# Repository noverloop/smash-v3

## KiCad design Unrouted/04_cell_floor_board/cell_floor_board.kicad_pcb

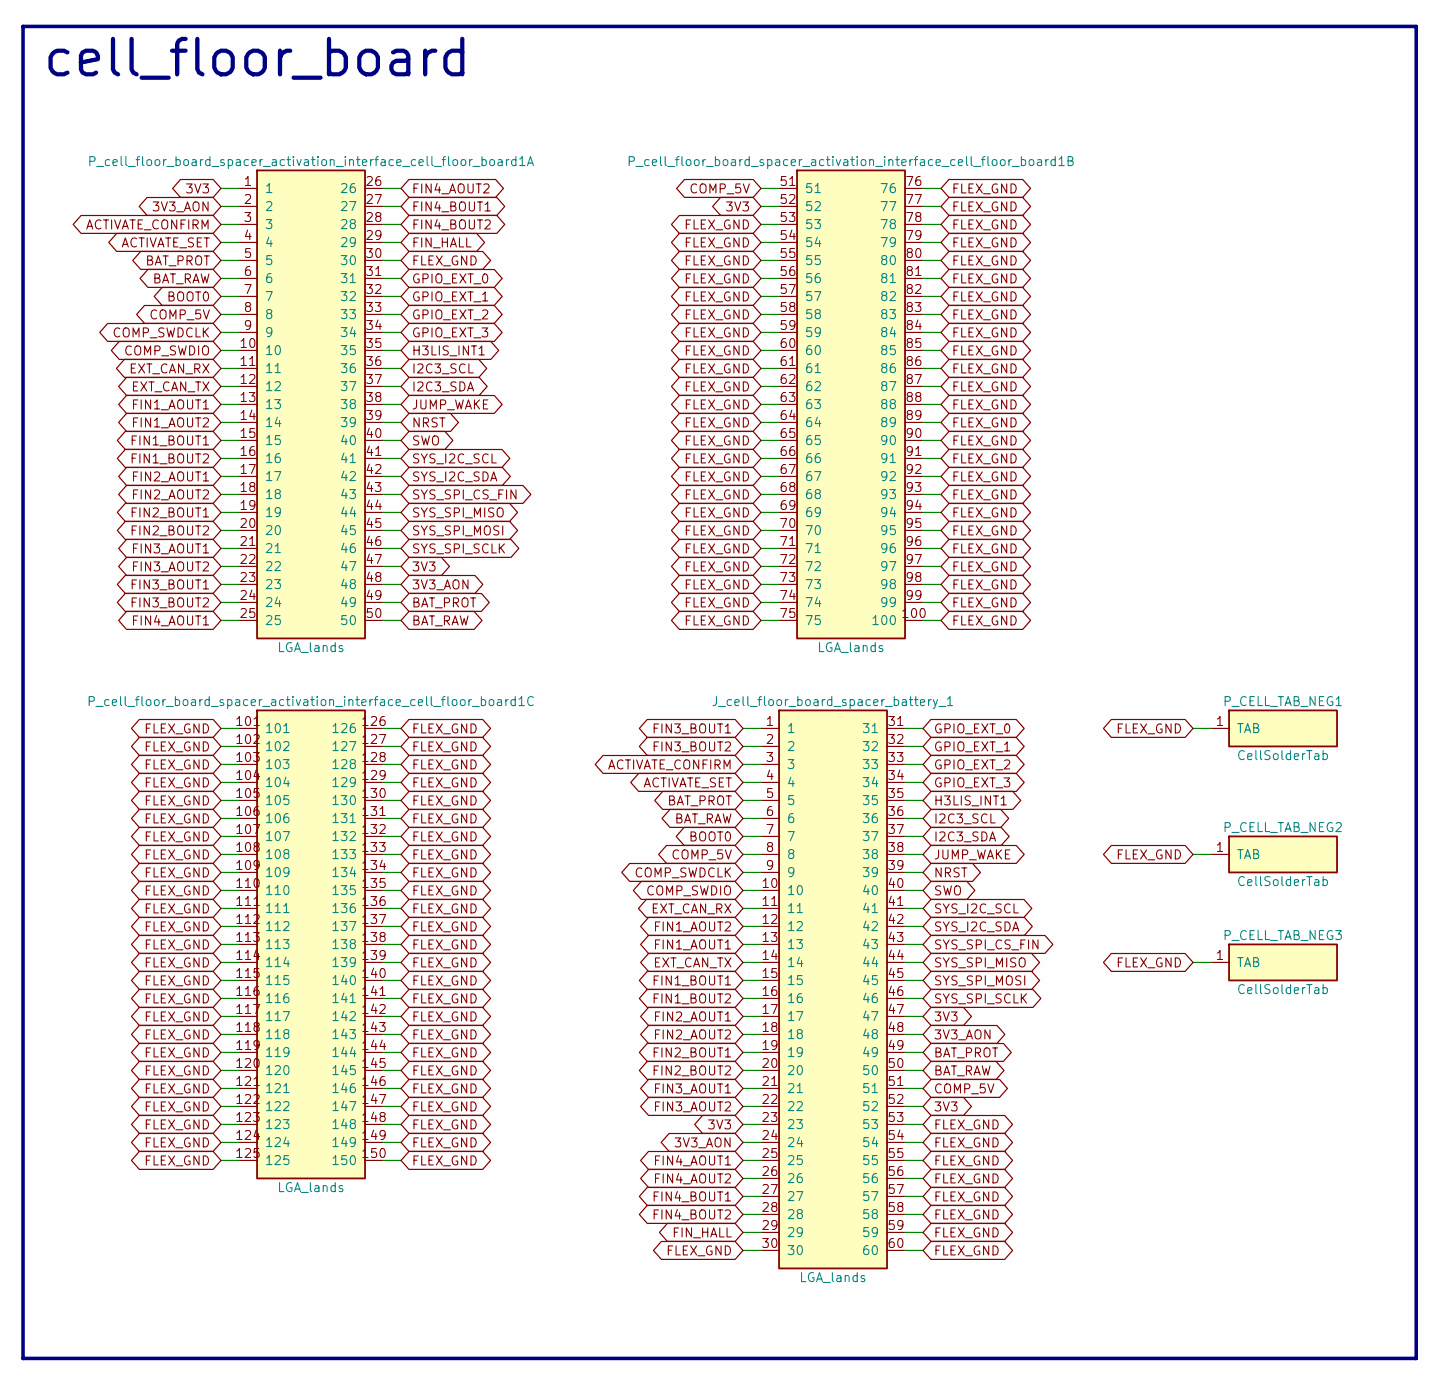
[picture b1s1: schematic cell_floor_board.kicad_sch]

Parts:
J_cell_floor_board_spacer_battery_1: LGA_lands; J_cell_floor_board_spacer_battery_1; MPN LGA_lands
P_CELL_TAB_NEG1, P_CELL_TAB_NEG2, P_CELL_TAB_NEG3: CellSolderTab; CellSolderTab_placeholder; MPN CellSolderTab
P_cell_floor_board_spacer_activation_interface_cell_floor_board1: LGA_lands; P_cell_floor_board_spacer_activation_interface_cell_floor_b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; MPN LGA_lands

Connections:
3V3: J_cell_floor_board_spacer_battery_1.23, J_cell_floor_board_spacer_battery_1.47, J_cell_floor_board_spacer_battery_1.52, P_cell_floor_board_spacer_activation_in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.1, P_cell_floor_board_spacer_activation_in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.47, P_cell_floor_board_spacer_activation_in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.52
3V3_AON: J_cell_floor_board_spacer_battery_1.24, J_cell_floor_board_spacer_battery_1.48, P_cell_floor_board_spacer_activation_in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.2, P_cell_floor_board_spacer_activation_in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.48
ACTIVATE_CONFIRM: J_cell_floor_board_spacer_battery_1.3, P_cell_floor_board_spacer_activation_in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.3
ACTIVATE_SET: J_cell_floor_board_spacer_battery_1.4, P_cell_floor_board_spacer_activation_in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.4
BAT_PROT: J_cell_floor_board_spacer_battery_1.5, J_cell_floor_board_spacer_battery_1.49, P_cell_floor_board_spacer_activation_in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.5, P_cell_floor_board_spacer_activation_in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.49
BAT_RAW: J_cell_floor_board_spacer_battery_1.6, J_cell_floor_board_spacer_battery_1.50, P_cell_floor_board_spacer_activation_in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.6, P_cell_floor_board_spacer_activation_in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.50
BOOT0: J_cell_floor_board_spacer_battery_1.7, P_cell_floor_board_spacer_activation_in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.7
COMP_5V: J_cell_floor_board_spacer_battery_1.8, J_cell_floor_board_spacer_battery_1.51, P_cell_floor_board_spacer_activation_in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.8, P_cell_floor_board_spacer_activation_in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.51
COMP_SWDCLK: J_cell_floor_board_spacer_battery_1.9, P_cell_floor_board_spacer_activation_in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.9
COMP_SWDIO: J_cell_floor_board_spacer_battery_1.10, P_cell_floor_board_spacer_activation_in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.10
EXT_CAN_RX: J_cell_floor_board_spacer_battery_1.11, P_cell_floor_board_spacer_activation_in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.11
EXT_CAN_TX: J_cell_floor_board_spacer_battery_1.14, P_cell_floor_board_spacer_activation_in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.12
FIN1_AOUT1: J_cell_floor_board_spacer_battery_1.13, P_cell_floor_board_spacer_activation_in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.13
FIN1_AOUT2: J_cell_floor_board_spacer_battery_1.12, P_cell_floor_board_spacer_activation_in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.14
FIN1_BOUT1: J_cell_floor_board_spacer_battery_1.15, P_cell_floor_board_spacer_activation_in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.15
FIN1_BOUT2: J_cell_floor_board_spacer_battery_1.16, P_cell_floor_board_spacer_activation_in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.16
FIN2_AOUT1: J_cell_floor_board_spacer_battery_1.17, P_cell_floor_board_spacer_activation_in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.17
FIN2_AOUT2: J_cell_floor_board_spacer_battery_1.18, P_cell_floor_board_spacer_activation_in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.18
FIN2_BOUT1: J_cell_floor_board_spacer_battery_1.19, P_cell_floor_board_spacer_activation_in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.19
FIN2_BOUT2: J_cell_floor_board_spacer_battery_1.20, P_cell_floor_board_spacer_activation_in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.20
FIN3_AOUT1: J_cell_floor_board_spacer_battery_1.21, P_cell_floor_board_spacer_activation_in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.21
FIN3_AOUT2: J_cell_floor_board_spacer_battery_1.22, P_cell_floor_board_spacer_activation_in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.22
FIN3_BOUT1: J_cell_floor_board_spacer_battery_1.1, P_cell_floor_board_spacer_activation_in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.23
FIN3_BOUT2: J_cell_floor_board_spacer_battery_1.2, P_cell_floor_board_spacer_activation_in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.24
FIN4_AOUT1: J_cell_floor_board_spacer_battery_1.25, P_cell_floor_board_spacer_activation_in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.25
FIN4_AOUT2: J_cell_floor_board_spacer_battery_1.26, P_cell_floor_board_spacer_activation_in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.26
FIN4_BOUT1: J_cell_floor_board_spacer_battery_1.27, P_cell_floor_board_spacer_activation_in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.27
FIN4_BOUT2: J_cell_floor_board_spacer_battery_1.28, P_cell_floor_board_spacer_activation_in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.28
FIN_HALL: J_cell_floor_board_spacer_battery_1.29, P_cell_floor_board_spacer_activation_in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.29
FLEX_GND: J_cell_floor_board_spacer_battery_1.30, J_cell_floor_board_spacer_battery_1.53, J_cell_floor_board_spacer_battery_1.54, J_cell_floor_board_spacer_battery_1.55, J_cell_floor_board_spacer_battery_1.56, J_cell_floor_board_spacer_battery_1.57, J_cell_floor_board_spacer_battery_1.58, J_cell_floor_board_spacer_battery_1.59, J_cell_floor_board_spacer_battery_1.60, P_CELL_TAB_NEG1.1, P_CELL_TAB_NEG2.1, P_CELL_TAB_NEG3.1, P_cell_floor_board_spacer_activation_in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.30, P_cell_floor_board_spacer_activation_in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.53, P_cell_floor_board_spacer_activation_in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.54, P_cell_floor_board_spacer_activation_in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.55, P_cell_floor_board_spacer_activation_in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.56, P_cell_floor_board_spacer_activation_in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.57, P_cell_floor_board_spacer_activation_in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.58, P_cell_floor_board_spacer_activation_in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.59, P_cell_floor_board_spacer_activation_in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.60, P_cell_floor_board_spacer_activation_in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.61, P_cell_floor_board_spacer_activation_in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.62, P_cell_floor_board_spacer_activation_in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.63, P_cell_floor_board_spacer_activation_in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.64, P_cell_floor_board_spacer_activation_in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.65, P_cell_floor_board_spacer_activation_in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.66, P_cell_floor_board_spacer_activation_in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.67, P_cell_floor_board_spacer_activation_in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.68, P_cell_floor_board_spacer_activation_in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.69, P_cell_floor_board_spacer_activation_in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.70, P_cell_floor_board_spacer_activation_in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.71, P_cell_floor_board_spacer_activation_in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.72, P_cell_floor_board_spacer_activation_in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.73, P_cell_floor_board_spacer_activation_in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.74, P_cell_floor_board_spacer_activation_in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.75, P_cell_floor_board_spacer_activation_in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.76, P_cell_floor_board_spacer_activation_in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.77, P_cell_floor_board_spacer_activation_in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.78, P_cell_floor_board_spacer_activation_in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.79, P_cell_floor_board_spacer_activation_in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.80, P_cell_floor_board_spacer_activation_in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.81, P_cell_floor_board_spacer_activation_in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.82, P_cell_floor_board_spacer_activation_in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.83, P_cell_floor_board_spacer_activation_in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.84, P_cell_floor_board_spacer_activation_in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.85, P_cell_floor_board_spacer_activation_in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.86, P_cell_floor_board_spacer_activation_in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.87, P_cell_floor_board_spacer_activation_in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.88, P_cell_floor_board_spacer_activation_in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.89, P_cell_floor_board_spacer_activation_in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.90, P_cell_floor_board_spacer_activation_in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.91, P_cell_floor_board_spacer_activation_in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.92, P_cell_floor_board_spacer_activation_in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.93, P_cell_floor_board_spacer_activation_in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.94, P_cell_floor_board_spacer_activation_in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.95, P_cell_floor_board_spacer_activation_in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.96, P_cell_floor_board_spacer_activation_in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.97, P_cell_floor_board_spacer_activation_in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.98, P_cell_floor_board_spacer_activation_in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.99, P_cell_floor_board_spacer_activation_in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.100, P_cell_floor_board_spacer_activation_in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.101, P_cell_floor_board_spacer_activation_in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.102, P_cell_floor_board_spacer_activation_in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.103, P_cell_floor_board_spacer_activation_in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.104, P_cell_floor_board_spacer_activation_in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.105, P_cell_floor_board_spacer_activation_in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.106, P_cell_floor_board_spacer_activation_in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.107, P_cell_floor_board_spacer_activation_in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.108, P_cell_floor_board_spacer_activation_in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.109, P_cell_floor_board_spacer_activation_in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.110, P_cell_floor_board_spacer_activation_in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.111, P_cell_floor_board_spacer_activation_in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.112, P_cell_floor_board_spacer_activation_in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.113, P_cell_floor_board_spacer_activation_in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.114, P_cell_floor_board_spacer_activation_in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.115, P_cell_floor_board_spacer_activation_in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.116, P_cell_floor_board_spacer_activation_in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.117, P_cell_floor_board_spacer_activation_in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.118, P_cell_floor_board_spacer_activation_in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.119, P_cell_floor_board_spacer_activation_in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.120, P_cell_floor_board_spacer_activation_in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.121, P_cell_floor_board_spacer_activation_in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.122, P_cell_floor_board_spacer_activation_in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.123, P_cell_floor_board_spacer_activation_in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.124, P_cell_floor_board_spacer_activation_in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.125, P_cell_floor_board_spacer_activation_in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.126, P_cell_floor_board_spacer_activation_in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.127, P_cell_floor_board_spacer_activation_in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.128, P_cell_floor_board_spacer_activation_in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.129, P_cell_floor_board_spacer_activation_in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.130, P_cell_floor_board_spacer_activation_in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.131, P_cell_floor_board_spacer_activation_in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.132, P_cell_floor_board_spacer_activation_in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.133, P_cell_floor_board_spacer_activation_in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.134, P_cell_floor_board_spacer_activation_in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.135, P_cell_floor_board_spacer_activation_in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.136, P_cell_floor_board_spacer_activation_in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.137, P_cell_floor_board_spacer_activation_in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.138, P_cell_floor_board_spacer_activation_in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.139, P_cell_floor_board_spacer_activation_in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.140, P_cell_floor_board_spacer_activation_in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.141, P_cell_floor_board_spacer_activation_in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.142, P_cell_floor_board_spacer_activation_in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.143, P_cell_floor_board_spacer_activation_in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.144, P_cell_floor_board_spacer_activation_in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.145, P_cell_floor_board_spacer_activation_in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.146, P_cell_floor_board_spacer_activation_in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.147, P_cell_floor_board_spacer_activation_in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.148, P_cell_floor_board_spacer_activation_in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.149, P_cell_floor_board_spacer_activation_in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.150
GPIO_EXT_0: J_cell_floor_board_spacer_battery_1.31, P_cell_floor_board_spacer_activation_in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.31
GPIO_EXT_1: J_cell_floor_board_spacer_battery_1.32, P_cell_floor_board_spacer_activation_in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.32
GPIO_EXT_2: J_cell_floor_board_spacer_battery_1.33, P_cell_floor_board_spacer_activation_in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.33
GPIO_EXT_3: J_cell_floor_board_spacer_battery_1.34, P_cell_floor_board_spacer_activation_in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.34
H3LIS_INT1: J_cell_floor_board_spacer_battery_1.35, P_cell_floor_board_spacer_activation_in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.35
I2C3_SCL: J_cell_floor_board_spacer_battery_1.36, P_cell_floor_board_spacer_activation_in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.36
I2C3_SDA: J_cell_floor_board_spacer_battery_1.37, P_cell_floor_board_spacer_activation_in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.37
JUMP_WAKE: J_cell_floor_board_spacer_battery_1.38, P_cell_floor_board_spacer_activation_in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.38
NRST: J_cell_floor_board_spacer_battery_1.39, P_cell_floor_board_spacer_activation_in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.39
SWO: J_cell_floor_board_spacer_battery_1.40, P_cell_floor_board_spacer_activation_in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.40
SYS_I2C_SCL: J_cell_floor_board_spacer_battery_1.41, P_cell_floor_board_spacer_activation_in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.41
SYS_I2C_SDA: J_cell_floor_board_spacer_battery_1.42, P_cell_floor_board_spacer_activation_in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.42
SYS_SPI_CS_FIN: J_cell_floor_board_spacer_battery_1.43, P_cell_floor_board_spacer_activation_in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.43
SYS_SPI_MISO: J_cell_floor_board_spacer_battery_1.44, P_cell_floor_board_spacer_activation_in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.44
SYS_SPI_MOSI: J_cell_floor_board_spacer_battery_1.45, P_cell_floor_board_spacer_activation_in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.45
SYS_SPI_SCLK: J_cell_floor_board_spacer_battery_1.46, P_cell_floor_board_spacer_activation_in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.46

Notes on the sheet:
cell_floor_board

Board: 6 copper layers, 7 parts (1 on the bottom side), 46 nets, no tracks yet.

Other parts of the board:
MH1, MH2: smash_mech_potting

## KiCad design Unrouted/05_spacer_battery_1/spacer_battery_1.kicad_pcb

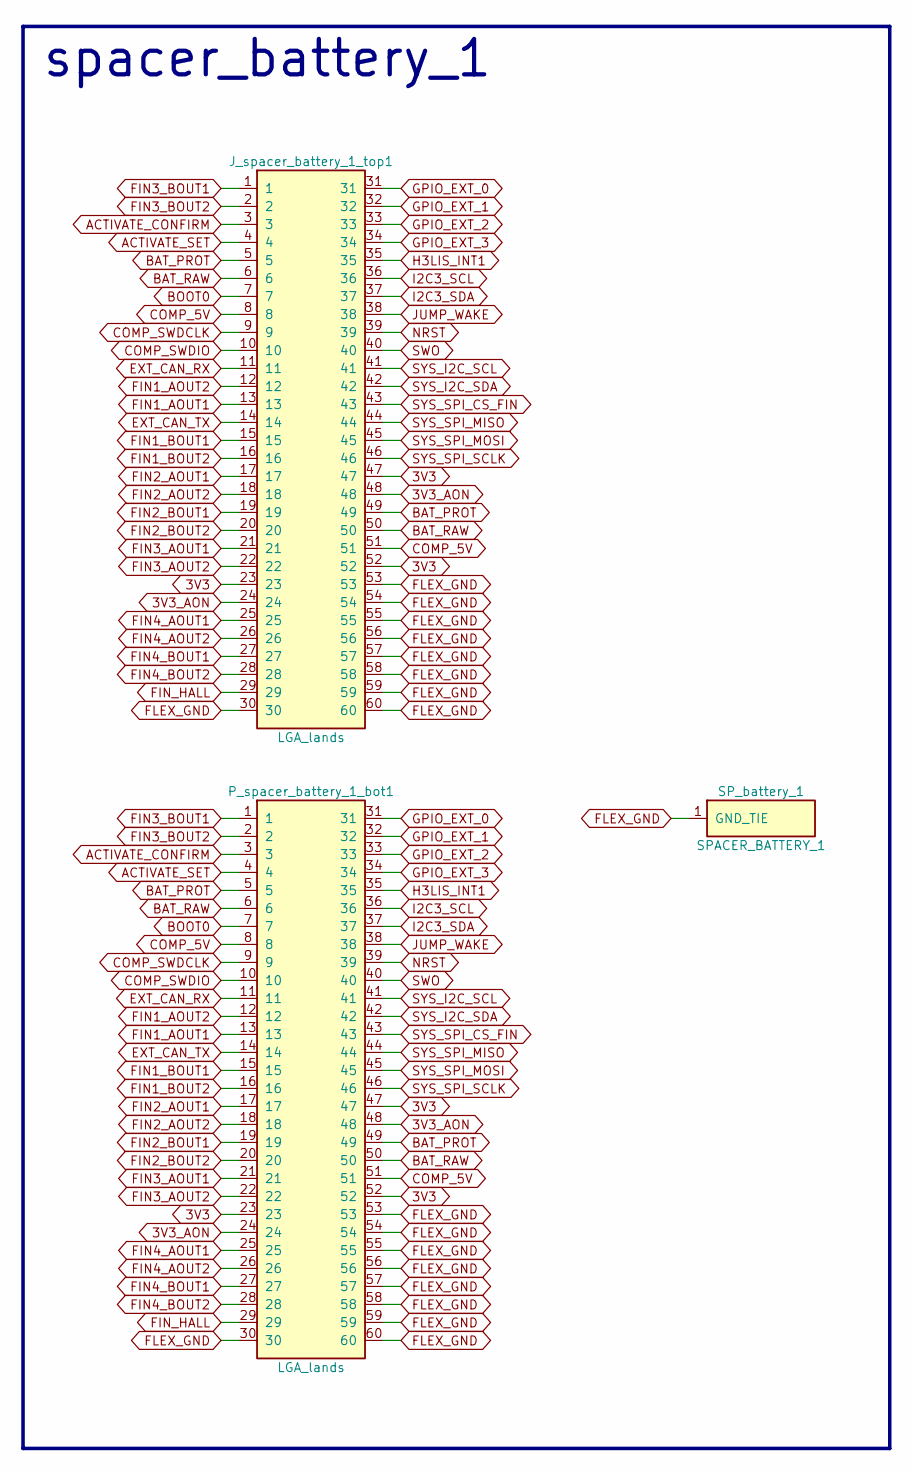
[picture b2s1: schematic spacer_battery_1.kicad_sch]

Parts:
J_spacer_battery_1_top1: LGA_lands; J_spacer_battery_1_top; MPN LGA_lands
P_spacer_battery_1_bot1: LGA_lands; P_spacer_battery_1_bot; MPN LGA_lands
SP_battery_1: SPACER_BATTERY_1; Spacer_Mechanical_34mm

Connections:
3V3: J_spacer_battery_1_top1.23, J_spacer_battery_1_top1.47, J_spacer_battery_1_top1.52, P_spacer_battery_1_bot1.23, P_spacer_battery_1_bot1.47, P_spacer_battery_1_bot1.52
3V3_AON: J_spacer_battery_1_top1.24, J_spacer_battery_1_top1.48, P_spacer_battery_1_bot1.24, P_spacer_battery_1_bot1.48
ACTIVATE_CONFIRM: J_spacer_battery_1_top1.3, P_spacer_battery_1_bot1.3
ACTIVATE_SET: J_spacer_battery_1_top1.4, P_spacer_battery_1_bot1.4
BAT_PROT: J_spacer_battery_1_top1.5, J_spacer_battery_1_top1.49, P_spacer_battery_1_bot1.5, P_spacer_battery_1_bot1.49
BAT_RAW: J_spacer_battery_1_top1.6, J_spacer_battery_1_top1.50, P_spacer_battery_1_bot1.6, P_spacer_battery_1_bot1.50
BOOT0: J_spacer_battery_1_top1.7, P_spacer_battery_1_bot1.7
COMP_5V: J_spacer_battery_1_top1.8, J_spacer_battery_1_top1.51, P_spacer_battery_1_bot1.8, P_spacer_battery_1_bot1.51
COMP_SWDCLK: J_spacer_battery_1_top1.9, P_spacer_battery_1_bot1.9
COMP_SWDIO: J_spacer_battery_1_top1.10, P_spacer_battery_1_bot1.10
EXT_CAN_RX: J_spacer_battery_1_top1.11, P_spacer_battery_1_bot1.11
EXT_CAN_TX: J_spacer_battery_1_top1.14, P_spacer_battery_1_bot1.14
FIN1_AOUT1: J_spacer_battery_1_top1.13, P_spacer_battery_1_bot1.13
FIN1_AOUT2: J_spacer_battery_1_top1.12, P_spacer_battery_1_bot1.12
FIN1_BOUT1: J_spacer_battery_1_top1.15, P_spacer_battery_1_bot1.15
FIN1_BOUT2: J_spacer_battery_1_top1.16, P_spacer_battery_1_bot1.16
FIN2_AOUT1: J_spacer_battery_1_top1.17, P_spacer_battery_1_bot1.17
FIN2_AOUT2: J_spacer_battery_1_top1.18, P_spacer_battery_1_bot1.18
FIN2_BOUT1: J_spacer_battery_1_top1.19, P_spacer_battery_1_bot1.19
FIN2_BOUT2: J_spacer_battery_1_top1.20, P_spacer_battery_1_bot1.20
FIN3_AOUT1: J_spacer_battery_1_top1.21, P_spacer_battery_1_bot1.21
FIN3_AOUT2: J_spacer_battery_1_top1.22, P_spacer_battery_1_bot1.22
FIN3_BOUT1: J_spacer_battery_1_top1.1, P_spacer_battery_1_bot1.1
FIN3_BOUT2: J_spacer_battery_1_top1.2, P_spacer_battery_1_bot1.2
FIN4_AOUT1: J_spacer_battery_1_top1.25, P_spacer_battery_1_bot1.25
FIN4_AOUT2: J_spacer_battery_1_top1.26, P_spacer_battery_1_bot1.26
FIN4_BOUT1: J_spacer_battery_1_top1.27, P_spacer_battery_1_bot1.27
FIN4_BOUT2: J_spacer_battery_1_top1.28, P_spacer_battery_1_bot1.28
FIN_HALL: J_spacer_battery_1_top1.29, P_spacer_battery_1_bot1.29
FLEX_GND: J_spacer_battery_1_top1.30, J_spacer_battery_1_top1.53, J_spacer_battery_1_top1.54, J_spacer_battery_1_top1.55, J_spacer_battery_1_top1.56, J_spacer_battery_1_top1.57, J_spacer_battery_1_top1.58, J_spacer_battery_1_top1.59, J_spacer_battery_1_top1.60, P_spacer_battery_1_bot1.30, P_spacer_battery_1_bot1.53, P_spacer_battery_1_bot1.54, P_spacer_battery_1_bot1.55, P_spacer_battery_1_bot1.56, P_spacer_battery_1_bot1.57, P_spacer_battery_1_bot1.58, P_spacer_battery_1_bot1.59, P_spacer_battery_1_bot1.60, SP_battery_1.1
GPIO_EXT_0: J_spacer_battery_1_top1.31, P_spacer_battery_1_bot1.31
GPIO_EXT_1: J_spacer_battery_1_top1.32, P_spacer_battery_1_bot1.32
GPIO_EXT_2: J_spacer_battery_1_top1.33, P_spacer_battery_1_bot1.33
GPIO_EXT_3: J_spacer_battery_1_top1.34, P_spacer_battery_1_bot1.34
H3LIS_INT1: J_spacer_battery_1_top1.35, P_spacer_battery_1_bot1.35
I2C3_SCL: J_spacer_battery_1_top1.36, P_spacer_battery_1_bot1.36
I2C3_SDA: J_spacer_battery_1_top1.37, P_spacer_battery_1_bot1.37
JUMP_WAKE: J_spacer_battery_1_top1.38, P_spacer_battery_1_bot1.38
NRST: J_spacer_battery_1_top1.39, P_spacer_battery_1_bot1.39
SWO: J_spacer_battery_1_top1.40, P_spacer_battery_1_bot1.40
SYS_I2C_SCL: J_spacer_battery_1_top1.41, P_spacer_battery_1_bot1.41
SYS_I2C_SDA: J_spacer_battery_1_top1.42, P_spacer_battery_1_bot1.42
SYS_SPI_CS_FIN: J_spacer_battery_1_top1.43, P_spacer_battery_1_bot1.43
SYS_SPI_MISO: J_spacer_battery_1_top1.44, P_spacer_battery_1_bot1.44
SYS_SPI_MOSI: J_spacer_battery_1_top1.45, P_spacer_battery_1_bot1.45
SYS_SPI_SCLK: J_spacer_battery_1_top1.46, P_spacer_battery_1_bot1.46

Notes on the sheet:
spacer_battery_1

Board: 2 copper layers, 4 parts (1 on the bottom side), 46 nets, no tracks yet.

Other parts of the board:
MH1: smash_mech_potting

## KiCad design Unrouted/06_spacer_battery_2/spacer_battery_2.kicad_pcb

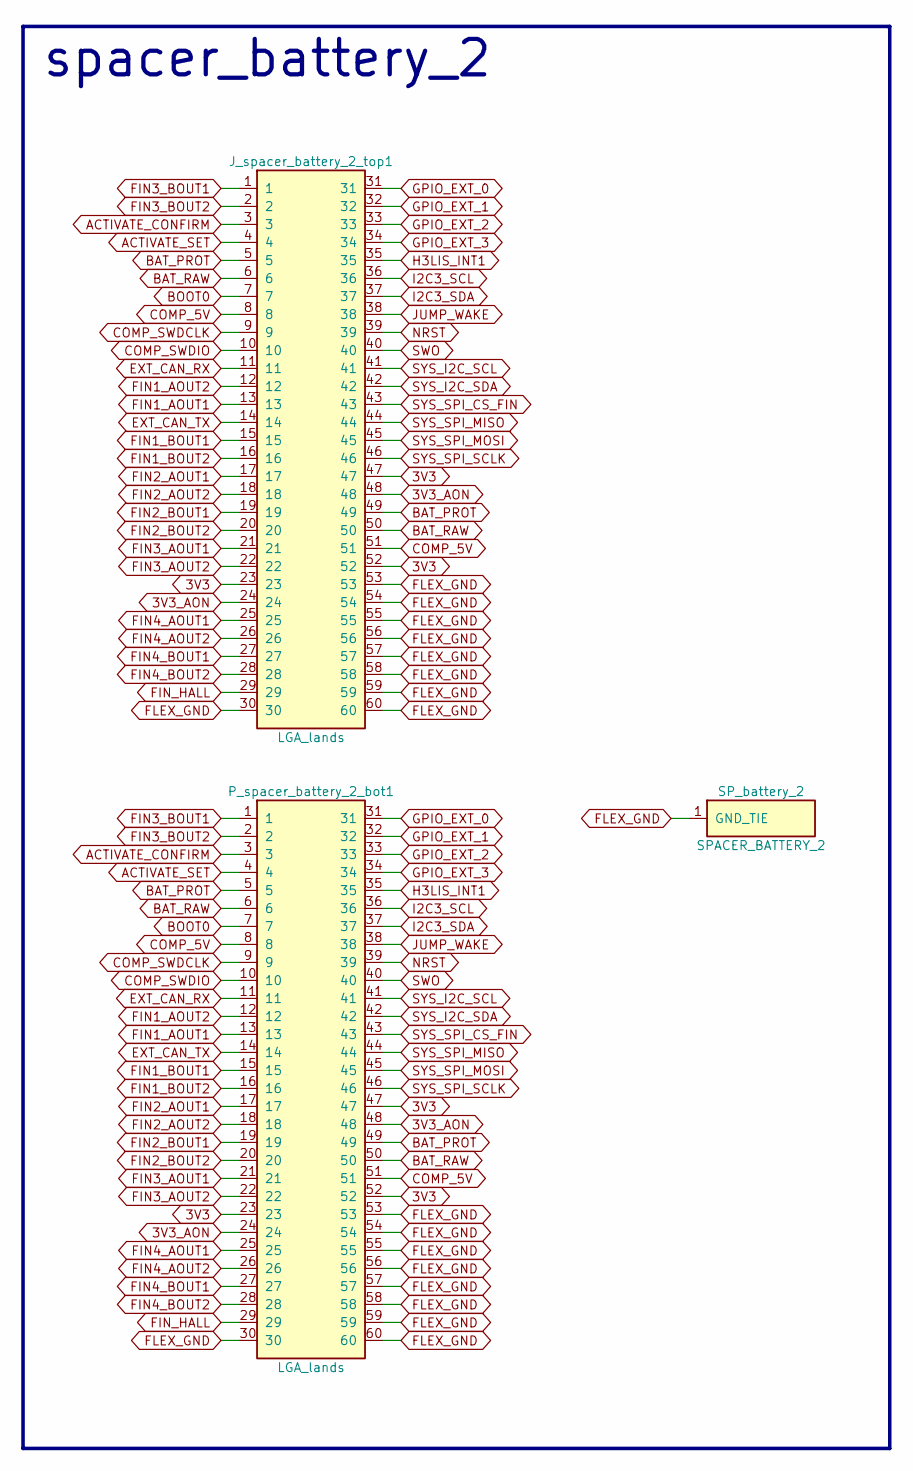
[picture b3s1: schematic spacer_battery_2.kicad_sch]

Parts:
J_spacer_battery_2_top1: LGA_lands; J_spacer_battery_2_top; MPN LGA_lands
P_spacer_battery_2_bot1: LGA_lands; P_spacer_battery_2_bot; MPN LGA_lands
SP_battery_2: SPACER_BATTERY_2; Spacer_Mechanical_34mm

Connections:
3V3: J_spacer_battery_2_top1.23, J_spacer_battery_2_top1.47, J_spacer_battery_2_top1.52, P_spacer_battery_2_bot1.23, P_spacer_battery_2_bot1.47, P_spacer_battery_2_bot1.52
3V3_AON: J_spacer_battery_2_top1.24, J_spacer_battery_2_top1.48, P_spacer_battery_2_bot1.24, P_spacer_battery_2_bot1.48
ACTIVATE_CONFIRM: J_spacer_battery_2_top1.3, P_spacer_battery_2_bot1.3
ACTIVATE_SET: J_spacer_battery_2_top1.4, P_spacer_battery_2_bot1.4
BAT_PROT: J_spacer_battery_2_top1.5, J_spacer_battery_2_top1.49, P_spacer_battery_2_bot1.5, P_spacer_battery_2_bot1.49
BAT_RAW: J_spacer_battery_2_top1.6, J_spacer_battery_2_top1.50, P_spacer_battery_2_bot1.6, P_spacer_battery_2_bot1.50
BOOT0: J_spacer_battery_2_top1.7, P_spacer_battery_2_bot1.7
COMP_5V: J_spacer_battery_2_top1.8, J_spacer_battery_2_top1.51, P_spacer_battery_2_bot1.8, P_spacer_battery_2_bot1.51
COMP_SWDCLK: J_spacer_battery_2_top1.9, P_spacer_battery_2_bot1.9
COMP_SWDIO: J_spacer_battery_2_top1.10, P_spacer_battery_2_bot1.10
EXT_CAN_RX: J_spacer_battery_2_top1.11, P_spacer_battery_2_bot1.11
EXT_CAN_TX: J_spacer_battery_2_top1.14, P_spacer_battery_2_bot1.14
FIN1_AOUT1: J_spacer_battery_2_top1.13, P_spacer_battery_2_bot1.13
FIN1_AOUT2: J_spacer_battery_2_top1.12, P_spacer_battery_2_bot1.12
FIN1_BOUT1: J_spacer_battery_2_top1.15, P_spacer_battery_2_bot1.15
FIN1_BOUT2: J_spacer_battery_2_top1.16, P_spacer_battery_2_bot1.16
FIN2_AOUT1: J_spacer_battery_2_top1.17, P_spacer_battery_2_bot1.17
FIN2_AOUT2: J_spacer_battery_2_top1.18, P_spacer_battery_2_bot1.18
FIN2_BOUT1: J_spacer_battery_2_top1.19, P_spacer_battery_2_bot1.19
FIN2_BOUT2: J_spacer_battery_2_top1.20, P_spacer_battery_2_bot1.20
FIN3_AOUT1: J_spacer_battery_2_top1.21, P_spacer_battery_2_bot1.21
FIN3_AOUT2: J_spacer_battery_2_top1.22, P_spacer_battery_2_bot1.22
FIN3_BOUT1: J_spacer_battery_2_top1.1, P_spacer_battery_2_bot1.1
FIN3_BOUT2: J_spacer_battery_2_top1.2, P_spacer_battery_2_bot1.2
FIN4_AOUT1: J_spacer_battery_2_top1.25, P_spacer_battery_2_bot1.25
FIN4_AOUT2: J_spacer_battery_2_top1.26, P_spacer_battery_2_bot1.26
FIN4_BOUT1: J_spacer_battery_2_top1.27, P_spacer_battery_2_bot1.27
FIN4_BOUT2: J_spacer_battery_2_top1.28, P_spacer_battery_2_bot1.28
FIN_HALL: J_spacer_battery_2_top1.29, P_spacer_battery_2_bot1.29
FLEX_GND: J_spacer_battery_2_top1.30, J_spacer_battery_2_top1.53, J_spacer_battery_2_top1.54, J_spacer_battery_2_top1.55, J_spacer_battery_2_top1.56, J_spacer_battery_2_top1.57, J_spacer_battery_2_top1.58, J_spacer_battery_2_top1.59, J_spacer_battery_2_top1.60, P_spacer_battery_2_bot1.30, P_spacer_battery_2_bot1.53, P_spacer_battery_2_bot1.54, P_spacer_battery_2_bot1.55, P_spacer_battery_2_bot1.56, P_spacer_battery_2_bot1.57, P_spacer_battery_2_bot1.58, P_spacer_battery_2_bot1.59, P_spacer_battery_2_bot1.60, SP_battery_2.1
GPIO_EXT_0: J_spacer_battery_2_top1.31, P_spacer_battery_2_bot1.31
GPIO_EXT_1: J_spacer_battery_2_top1.32, P_spacer_battery_2_bot1.32
GPIO_EXT_2: J_spacer_battery_2_top1.33, P_spacer_battery_2_bot1.33
GPIO_EXT_3: J_spacer_battery_2_top1.34, P_spacer_battery_2_bot1.34
H3LIS_INT1: J_spacer_battery_2_top1.35, P_spacer_battery_2_bot1.35
I2C3_SCL: J_spacer_battery_2_top1.36, P_spacer_battery_2_bot1.36
I2C3_SDA: J_spacer_battery_2_top1.37, P_spacer_battery_2_bot1.37
JUMP_WAKE: J_spacer_battery_2_top1.38, P_spacer_battery_2_bot1.38
NRST: J_spacer_battery_2_top1.39, P_spacer_battery_2_bot1.39
SWO: J_spacer_battery_2_top1.40, P_spacer_battery_2_bot1.40
SYS_I2C_SCL: J_spacer_battery_2_top1.41, P_spacer_battery_2_bot1.41
SYS_I2C_SDA: J_spacer_battery_2_top1.42, P_spacer_battery_2_bot1.42
SYS_SPI_CS_FIN: J_spacer_battery_2_top1.43, P_spacer_battery_2_bot1.43
SYS_SPI_MISO: J_spacer_battery_2_top1.44, P_spacer_battery_2_bot1.44
SYS_SPI_MOSI: J_spacer_battery_2_top1.45, P_spacer_battery_2_bot1.45
SYS_SPI_SCLK: J_spacer_battery_2_top1.46, P_spacer_battery_2_bot1.46

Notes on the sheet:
spacer_battery_2

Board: 2 copper layers, 4 parts (1 on the bottom side), 46 nets, no tracks yet.

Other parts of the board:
MH1: smash_mech_potting

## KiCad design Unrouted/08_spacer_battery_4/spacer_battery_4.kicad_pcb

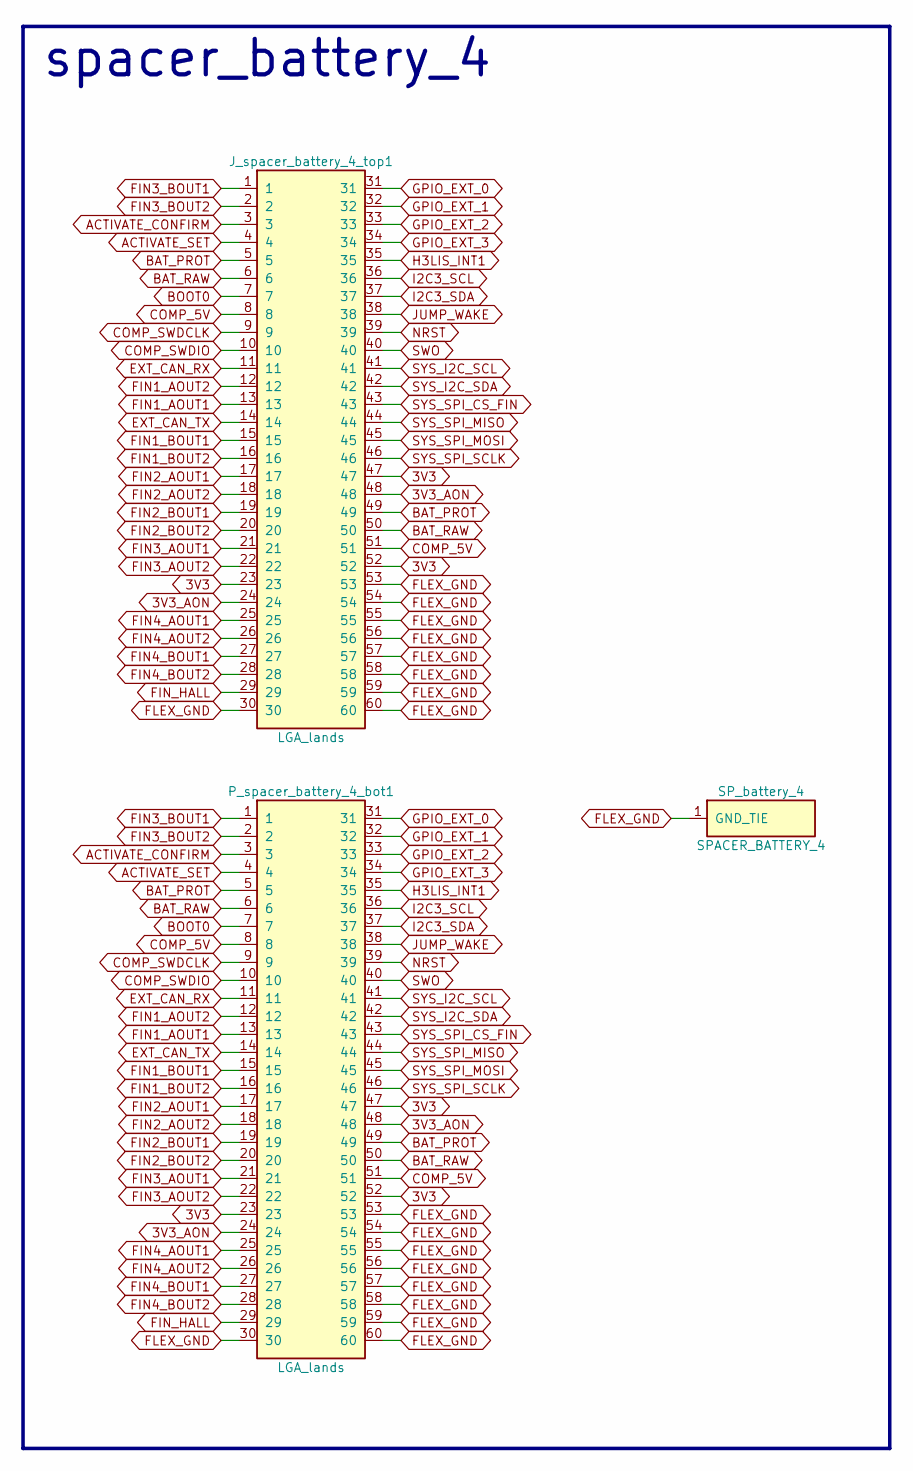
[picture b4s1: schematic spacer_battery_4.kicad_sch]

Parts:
J_spacer_battery_4_top1: LGA_lands; J_spacer_battery_4_top; MPN LGA_lands
P_spacer_battery_4_bot1: LGA_lands; P_spacer_battery_4_bot; MPN LGA_lands
SP_battery_4: SPACER_BATTERY_4; Spacer_Mechanical_34mm

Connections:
3V3: J_spacer_battery_4_top1.23, J_spacer_battery_4_top1.47, J_spacer_battery_4_top1.52, P_spacer_battery_4_bot1.23, P_spacer_battery_4_bot1.47, P_spacer_battery_4_bot1.52
3V3_AON: J_spacer_battery_4_top1.24, J_spacer_battery_4_top1.48, P_spacer_battery_4_bot1.24, P_spacer_battery_4_bot1.48
ACTIVATE_CONFIRM: J_spacer_battery_4_top1.3, P_spacer_battery_4_bot1.3
ACTIVATE_SET: J_spacer_battery_4_top1.4, P_spacer_battery_4_bot1.4
BAT_PROT: J_spacer_battery_4_top1.5, J_spacer_battery_4_top1.49, P_spacer_battery_4_bot1.5, P_spacer_battery_4_bot1.49
BAT_RAW: J_spacer_battery_4_top1.6, J_spacer_battery_4_top1.50, P_spacer_battery_4_bot1.6, P_spacer_battery_4_bot1.50
BOOT0: J_spacer_battery_4_top1.7, P_spacer_battery_4_bot1.7
COMP_5V: J_spacer_battery_4_top1.8, J_spacer_battery_4_top1.51, P_spacer_battery_4_bot1.8, P_spacer_battery_4_bot1.51
COMP_SWDCLK: J_spacer_battery_4_top1.9, P_spacer_battery_4_bot1.9
COMP_SWDIO: J_spacer_battery_4_top1.10, P_spacer_battery_4_bot1.10
EXT_CAN_RX: J_spacer_battery_4_top1.11, P_spacer_battery_4_bot1.11
EXT_CAN_TX: J_spacer_battery_4_top1.14, P_spacer_battery_4_bot1.14
FIN1_AOUT1: J_spacer_battery_4_top1.13, P_spacer_battery_4_bot1.13
FIN1_AOUT2: J_spacer_battery_4_top1.12, P_spacer_battery_4_bot1.12
FIN1_BOUT1: J_spacer_battery_4_top1.15, P_spacer_battery_4_bot1.15
FIN1_BOUT2: J_spacer_battery_4_top1.16, P_spacer_battery_4_bot1.16
FIN2_AOUT1: J_spacer_battery_4_top1.17, P_spacer_battery_4_bot1.17
FIN2_AOUT2: J_spacer_battery_4_top1.18, P_spacer_battery_4_bot1.18
FIN2_BOUT1: J_spacer_battery_4_top1.19, P_spacer_battery_4_bot1.19
FIN2_BOUT2: J_spacer_battery_4_top1.20, P_spacer_battery_4_bot1.20
FIN3_AOUT1: J_spacer_battery_4_top1.21, P_spacer_battery_4_bot1.21
FIN3_AOUT2: J_spacer_battery_4_top1.22, P_spacer_battery_4_bot1.22
FIN3_BOUT1: J_spacer_battery_4_top1.1, P_spacer_battery_4_bot1.1
FIN3_BOUT2: J_spacer_battery_4_top1.2, P_spacer_battery_4_bot1.2
FIN4_AOUT1: J_spacer_battery_4_top1.25, P_spacer_battery_4_bot1.25
FIN4_AOUT2: J_spacer_battery_4_top1.26, P_spacer_battery_4_bot1.26
FIN4_BOUT1: J_spacer_battery_4_top1.27, P_spacer_battery_4_bot1.27
FIN4_BOUT2: J_spacer_battery_4_top1.28, P_spacer_battery_4_bot1.28
FIN_HALL: J_spacer_battery_4_top1.29, P_spacer_battery_4_bot1.29
FLEX_GND: J_spacer_battery_4_top1.30, J_spacer_battery_4_top1.53, J_spacer_battery_4_top1.54, J_spacer_battery_4_top1.55, J_spacer_battery_4_top1.56, J_spacer_battery_4_top1.57, J_spacer_battery_4_top1.58, J_spacer_battery_4_top1.59, J_spacer_battery_4_top1.60, P_spacer_battery_4_bot1.30, P_spacer_battery_4_bot1.53, P_spacer_battery_4_bot1.54, P_spacer_battery_4_bot1.55, P_spacer_battery_4_bot1.56, P_spacer_battery_4_bot1.57, P_spacer_battery_4_bot1.58, P_spacer_battery_4_bot1.59, P_spacer_battery_4_bot1.60, SP_battery_4.1
GPIO_EXT_0: J_spacer_battery_4_top1.31, P_spacer_battery_4_bot1.31
GPIO_EXT_1: J_spacer_battery_4_top1.32, P_spacer_battery_4_bot1.32
GPIO_EXT_2: J_spacer_battery_4_top1.33, P_spacer_battery_4_bot1.33
GPIO_EXT_3: J_spacer_battery_4_top1.34, P_spacer_battery_4_bot1.34
H3LIS_INT1: J_spacer_battery_4_top1.35, P_spacer_battery_4_bot1.35
I2C3_SCL: J_spacer_battery_4_top1.36, P_spacer_battery_4_bot1.36
I2C3_SDA: J_spacer_battery_4_top1.37, P_spacer_battery_4_bot1.37
JUMP_WAKE: J_spacer_battery_4_top1.38, P_spacer_battery_4_bot1.38
NRST: J_spacer_battery_4_top1.39, P_spacer_battery_4_bot1.39
SWO: J_spacer_battery_4_top1.40, P_spacer_battery_4_bot1.40
SYS_I2C_SCL: J_spacer_battery_4_top1.41, P_spacer_battery_4_bot1.41
SYS_I2C_SDA: J_spacer_battery_4_top1.42, P_spacer_battery_4_bot1.42
SYS_SPI_CS_FIN: J_spacer_battery_4_top1.43, P_spacer_battery_4_bot1.43
SYS_SPI_MISO: J_spacer_battery_4_top1.44, P_spacer_battery_4_bot1.44
SYS_SPI_MOSI: J_spacer_battery_4_top1.45, P_spacer_battery_4_bot1.45
SYS_SPI_SCLK: J_spacer_battery_4_top1.46, P_spacer_battery_4_bot1.46

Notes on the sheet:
spacer_battery_4

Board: 2 copper layers, 4 parts (1 on the bottom side), 46 nets, no tracks yet.

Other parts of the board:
MH1: smash_mech_potting
